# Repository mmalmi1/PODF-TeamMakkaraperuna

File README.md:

# PODF-TeamMakkaraperuna
Repository

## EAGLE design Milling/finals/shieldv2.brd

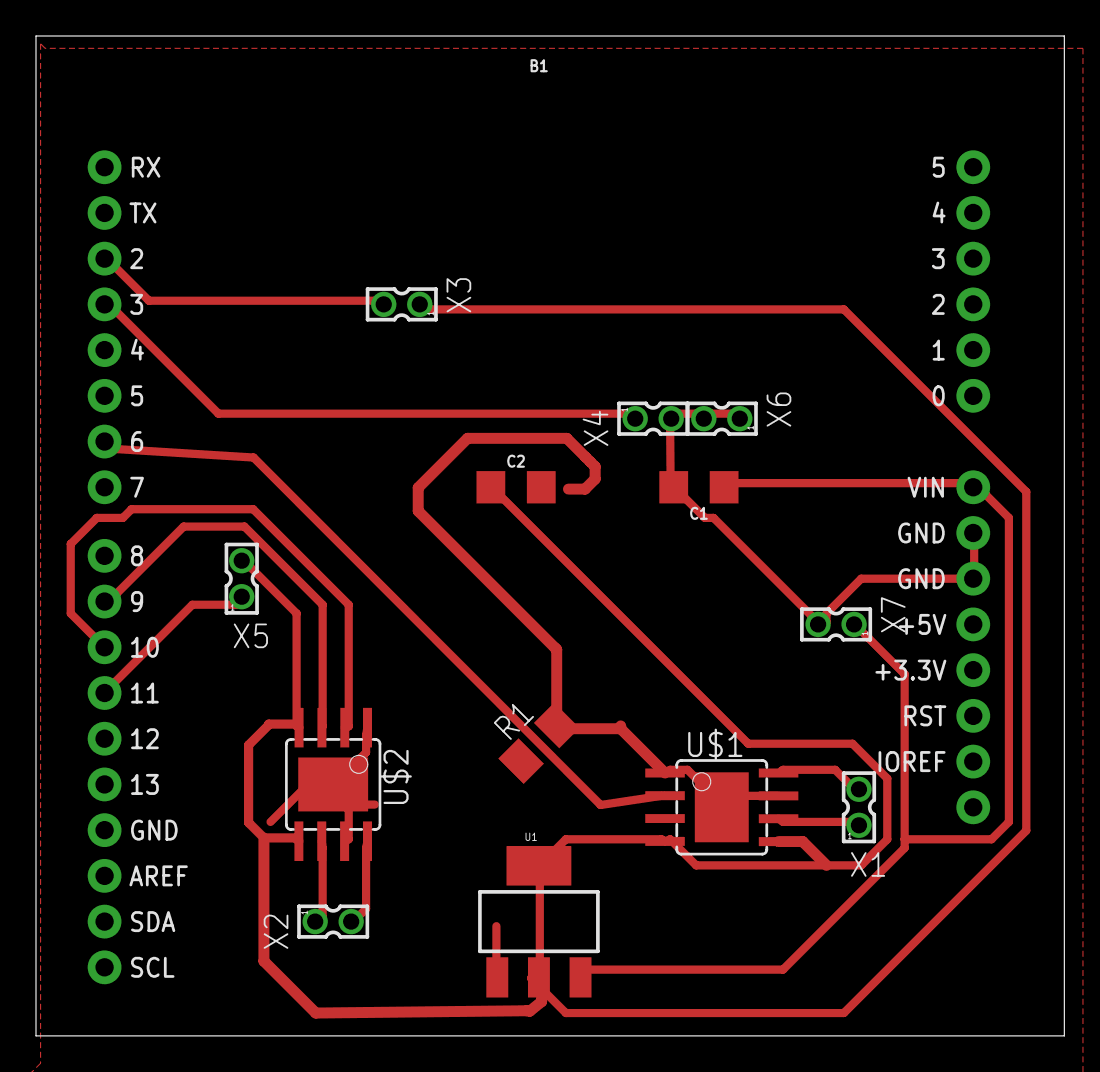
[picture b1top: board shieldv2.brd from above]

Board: 2 copper layers, 57.1 x 55.6 mm, 14 parts (0 on the bottom side), 15 nets.

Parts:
B1: ARDUINO_UNO_R3_SHIELDBASIC; UNO_R3_SHIELD
C1, C2: 10uF; 1206
R1: M1206
U1: SOT223
U$1, U$2: A4953-H-BRIDGE-MOTOR-DRIVER-PAD; SOIC8_PAD
X1, X2, X3, X4, X5, X6, X7: 332-02

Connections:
+5V: C2.1, U1.2, U1.4, U$1.4, U$1.5, X3.1
unnamed: B1.GND@0, B1.GND@1, B1.GND@2, C1.2, C2.2, R1.1, R1.2, U1.1, U$1.1, U$1.7, U$1.GND, U$2.1, U$2.7, U$2.GND, X4.2, X6.1, X6.2, X7.2
unnamed: B1.D6, U$1.2
unnamed: U$1.8, X1.2
unnamed: B1.D10, U$2.2
unnamed: U$1.6, X1.1
unnamed: U$2.8, X2.2
unnamed: U$2.6, X2.1
unnamed: B1.D5, U$1.3
unnamed: B1.D3, X4.1
unnamed: B1.D2, X3.2
unnamed: B1.D11, X5.1
unnamed: B1.D9, U$2.3
S$2: U$2.4, U$2.5, X5.2
VCC: B1.VIN, C1.1, U1.3, X7.1

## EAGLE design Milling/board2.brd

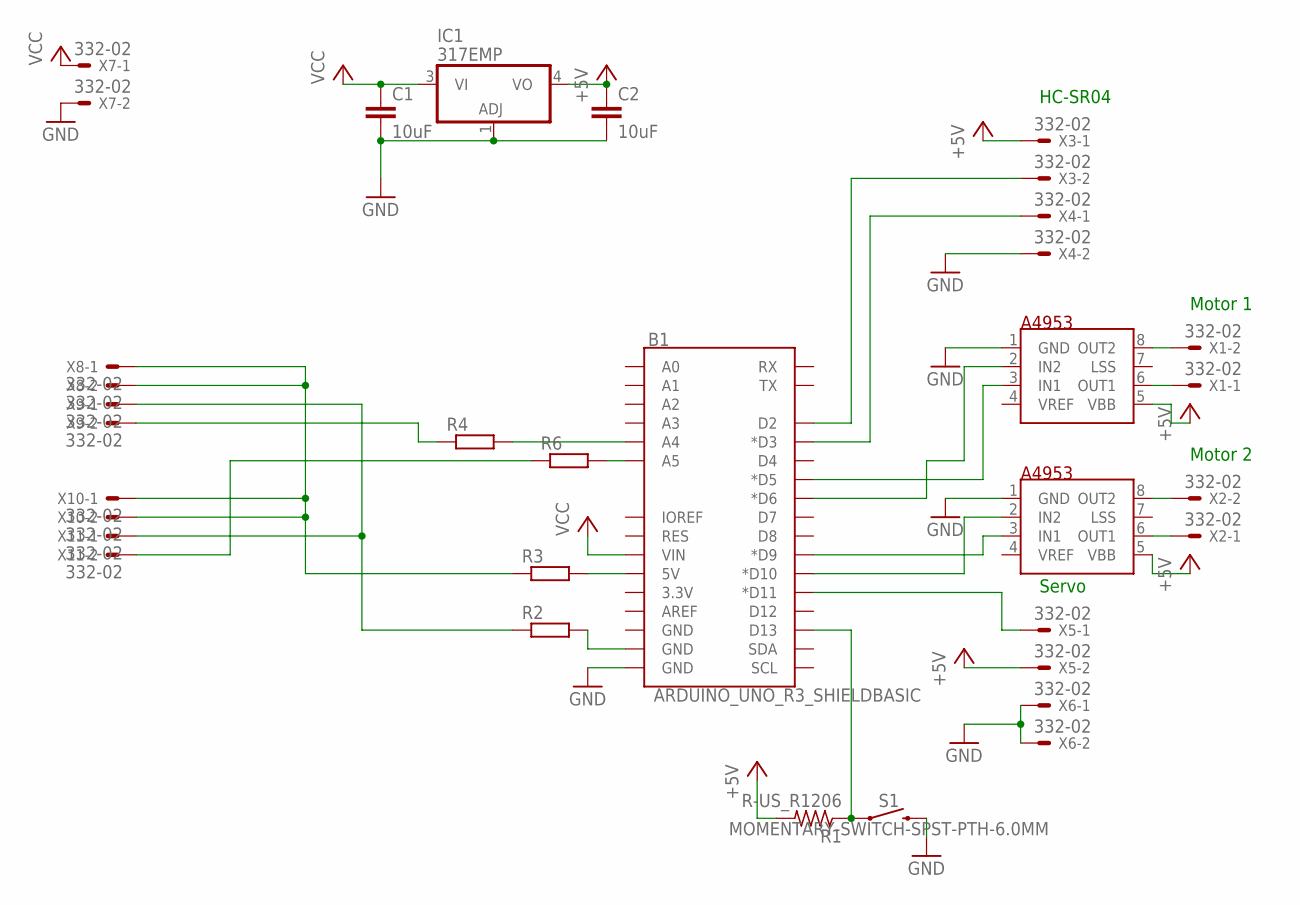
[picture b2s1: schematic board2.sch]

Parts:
A1, A2: A4953; SO08
B1: ARDUINO_UNO_R3_SHIELDBASIC; UNO_R3_SHIELD
C1, C2: 10uF; 1206
IC1: 317EMP; SOT223
R1: R-US_R1206; R1206
R2, R3, R4, R6: RR1206; R1206
S1: MOMENTARY-SWITCH-SPST-PTH-6.0MM; TACTILE_SWITCH_PTH_6.0MM
X1, X2, X3, X4, X5, X6, X7, X8, X9, X10, X11: 332-02

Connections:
+5V: A1.5 (VBB), A2.5 (VBB), C2.1, IC1.4 (VO), R1.2, X3.1, X5.2
GND: A1.1 (GND), A2.1 (GND), B1.GND@0 (GND), C1.2, C2.2, IC1.1 (ADJ), S1.3 (2), X4.2, X6.1, X6.2, X7.2
unnamed: A1.3 (IN1), B1.D5 (*D5)
unnamed: A1.2 (IN2), B1.D6 (*D6)
unnamed: A2.3 (IN1), B1.D9 (*D9)
unnamed: A2.2 (IN2), B1.D10 (*D10)
unnamed: A1.6 (OUT1), X1.1
unnamed: A1.8 (OUT2), X1.2
unnamed: A2.6 (OUT1), X2.1
unnamed: A2.8 (OUT2), X2.2
unnamed: B1.D3 (*D3), X4.1
unnamed: B1.D2, X3.2
unnamed: B1.D11 (*D11), X5.1
unnamed: B1.D13, R1.1, S1.1
unnamed: B1.A4, R4.2
unnamed: R3.1, X8.1, X8.2, X10.1, X10.2
unnamed: R2.1, X9.1, X11.1
unnamed: B1.GND@1 (GND), R2.2
unnamed: R4.1, X9.2
unnamed: B1.5V, R3.2
unnamed: B1.A5, R6.2
unnamed: R6.1, X11.2
VCC: B1.VIN, C1.1, IC1.3 (VI), X7.1

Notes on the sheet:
Motor 1
Motor 2
Servo
HC-SR04

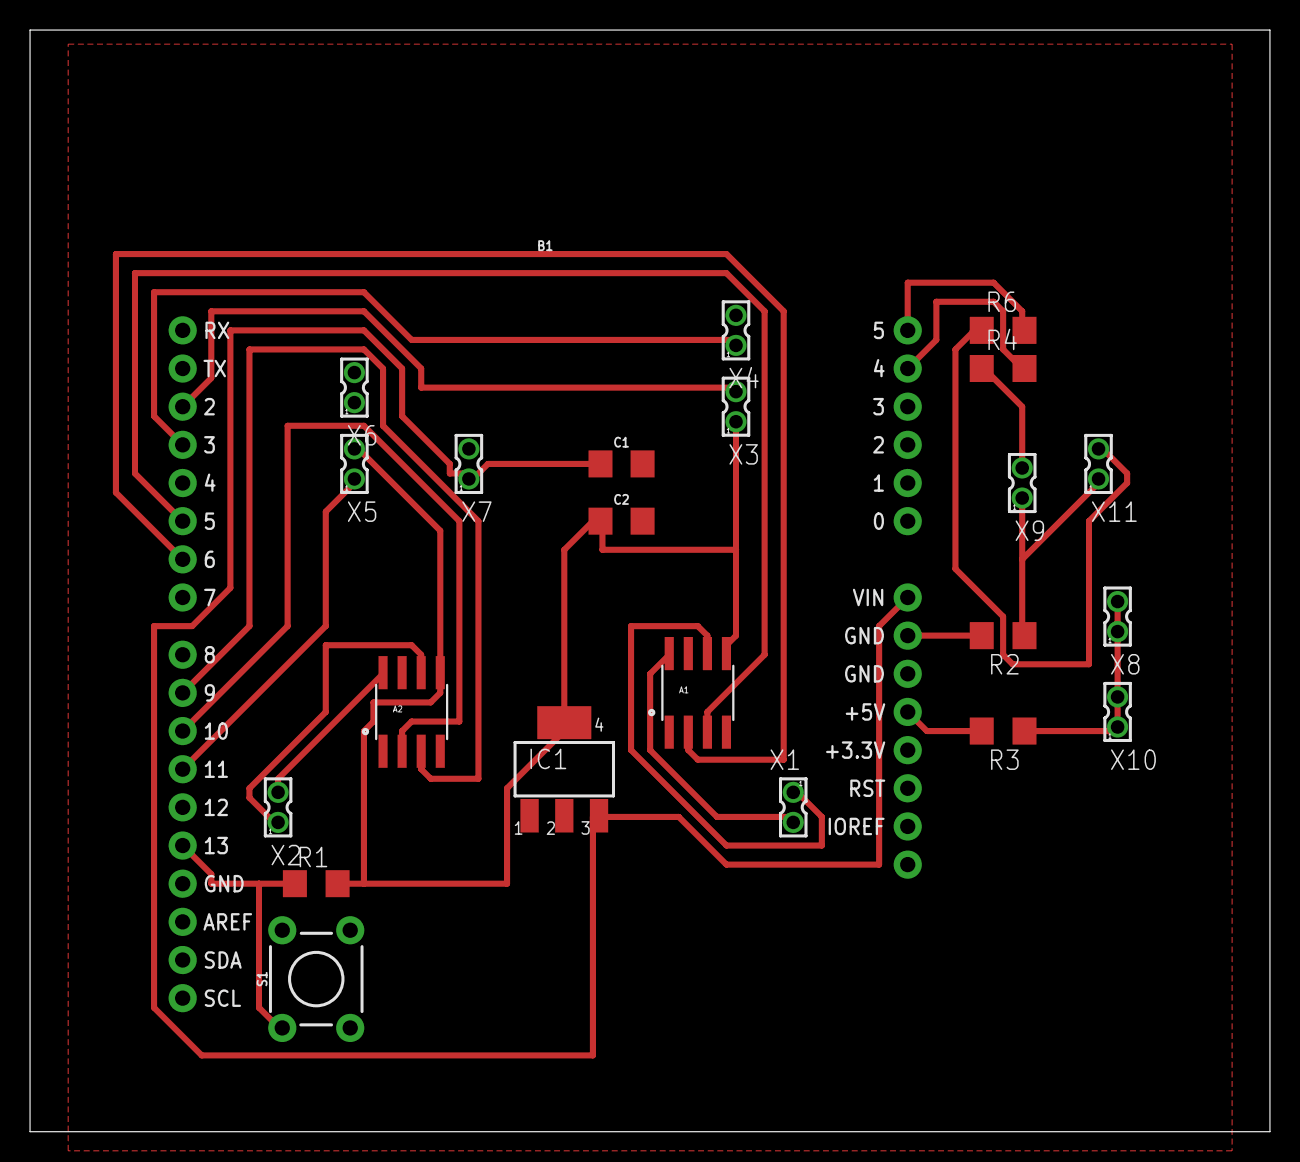
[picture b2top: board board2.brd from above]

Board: 2 copper layers, 82.5 x 73.3 mm, 23 parts (0 on the bottom side), 23 nets.

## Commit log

2018-03-20 https://github.com/mmalmi1/PODF-TeamMakkaraperuna.git
2018-03-20 sdasdasd
2018-03-20 updeitti
2018-03-20 Hello animals
2018-03-20 Hello animals v2
2018-03-20 removed useless .txt
2018-03-20 Branch 2
2018-03-20 Me too
2018-03-20 SIck codes
2018-03-20 removedfile
2018-03-21 Lisäsin component listin
2018-04-11 Added bill of materials
2018-04-11 Edited bill of materials
2018-05-03 Adding milling files
2018-05-03 fixed eagle files
2018-05-04 added laser cut files
2018-05-04 Adding code
2018-05-05 added code libraries
2018-05-06 fixing bugs
2018-05-07 Made servo spin and check for walls
2018-05-08 updated code
2018-05-09 Added pptx
2018-05-09 typo corrected
2018-05-09 added gif
2018-05-14 added board file
2018-05-16 added pmw and turning
2018-05-17 added code
2018-05-17 Fixed typo
2018-05-17 Added 3D printed files
2018-05-18 Wrapping up
2018-05-27 final code

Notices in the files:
parts and their libraries:
SparkFun-IC-Power: Licensing: Creative Commons ShareAlike 4.0 International - https://creativecommons.org/licenses/by-sa/4.0
